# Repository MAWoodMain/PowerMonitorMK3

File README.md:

# Power Meter MK3

## The Plan

The plan is to evaluate the ADE9153 IC using an initial PCB build with mains isolation for easy development and no real planned form factor.

Then assuming the IC checks out the schematic and PCB will be reissued without isolation and with a much tigher form factor to fit in a DIN rail enclosure so it can be wired into my home.

An extra prototype run may be required inbetween to evaluate isolation removal or to fix mistakes that render ISS1 unusable.

The ISS1 PCB is powered from the safe side using a micro USB cable and this power is isolated and used on the hot side, this circuit is based on the ADE9153's evaluation board schematic. 

**It is noteworthy that the hot side's GND is mains live and does present a serious safety risk.**

I accept no liability for anyone else's use of this design.

## PCB Builds

### ISS1 Build:
- PCB ordered from JLC PCB
  - ENIG finish
  - 1.6mm FR4
  - Top side stencil order with the PCB
    - Ordered default size, this was a mistake next time order a custom side much smaller
- Parts ordered from LCSC and DigiKey kitting for 2 PCBs
  - DHL on behalf of Digikey charged excessive customs charges inflating the build cost greatly I recommend Mouser as an alternative (for the UK) and have upissued the BOM accordingly
- Assembled at home
  - Boards were cleaned with IPA
  - Scrap PCBs were used to position the new PCB in place for stenciling
  - Paste was squeegeed onto the boards using a scrap piece of ceramic with a very flat edge
  - All components were hand placed with tweezers
  - The board was placed on a temperature controlled hotplate at 150°C
  - Once the board was evenly preheated (confirmed with IR thermometer) 350°C hot air was used to reflow the components
  - Some joints were not fully reflowed so touchups were performed with a fine soldering tip and extra liquid flux
  - The ADE9153 IC is in a QFN package which is difficult to manage as a hobbiest so reflow did yield some shorts on the edges, the shorts were manually reworked with extra flux and a fine tip.
  - Fortunatly the guard trace around the VAMS did not short to GND or VAMS, the layout recommendations from AD were to expose copper under the QFN which posed a high risk of soldering shorts.
  - The board was then cleaned with flux clean and IPA
  - All hand soldered components were soldered normally
  - A final clean was performed with flux clean

#### Issues associated with this build:
[#1](/../../issues/1) [#2](/../../issues/2) [#3](/../../issues/3)
#### Board mods:
- **MOD A** 
  - Pin 5 of U2 (Isolated DC-DC) has to be isolated, the PCB connects it to GND which prevents the IC from working
     - I cut the leg off the IC to isolate it

- **MOD B** 
  - ESP32-Wrover pins 17-22 cannot be used as they are used internally
     - I cut NC jumpers JP5, JP6 & JP7, the both sides of all three jumpers is reserved for internal use so manual wire mods will be needed lated to connect these to appropriate pins

## Firmware development

Currently in hardware testing phase, temporary non VCS projects are being used to evaluate the PCB, once this process is complete a formal firmware project will be added to VCS and developed

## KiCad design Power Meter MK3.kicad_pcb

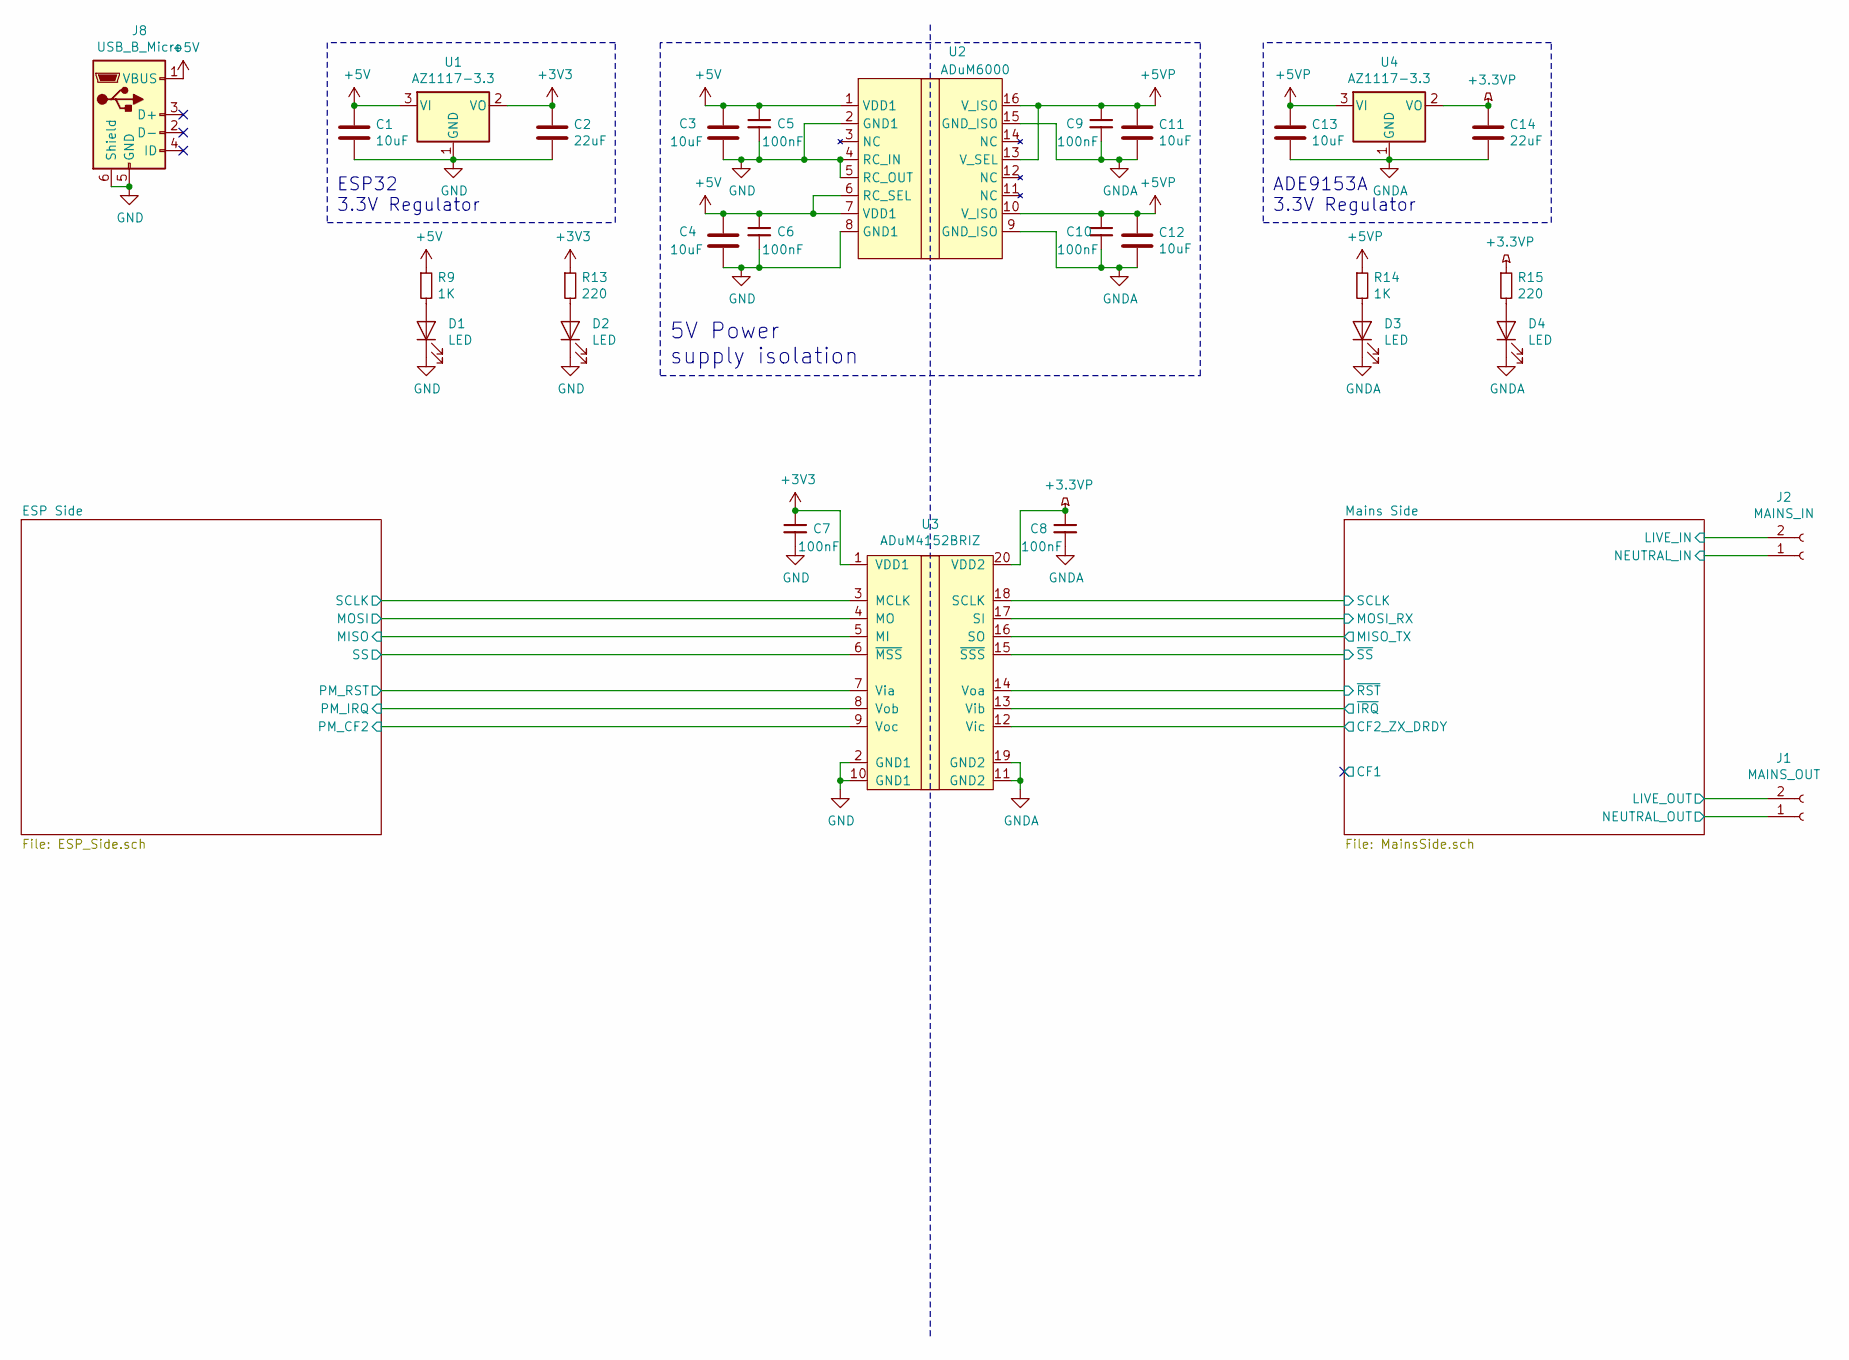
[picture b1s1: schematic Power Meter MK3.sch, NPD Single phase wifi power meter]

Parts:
C1, C3, C4, C11, C12, C13: 10uF; C_0603_1608Metric
C2, C14: 22uF; C_0603_1608Metric
C5, C6, C7, C8, C9, C10: 100nF; C_0603_1608Metric
D1, D2, D3, D4: LED; LED_0603_1608Metric
J1: MAINS_OUT; PHOENIX_1792229
J2: MAINS_IN; PHOENIX_1792229
J8: USB_B_Micro; USB_Micro-B_Molex_47346-0001
R9, R14: 1K; R_0603_1608Metric
R13, R15: 220; R_0603_1608Metric
U1, U4: AZ1117-3.3; SOT-223-3_TabPin2
U2: ADuM6000; SOIC-16W_7.5x10.3mm_P1.27mm
U3: ADuM4152BRIZ; SOIC-20W_7.5x12.8mm_P1.27mm

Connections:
+3.3VP: C8.1, C14.1, R15.1, U3.20 (VDD2), U4.2 (VO); also elsewhere on the board
+3V3: C2.1, C7.1, R13.1, U1.2 (VO), U3.1 (VDD1); also elsewhere on the board
+5V: C1.1, C3.1, C4.1, C5.1, C6.1, J8.1 (VBUS), R9.1, U1.3 (VI), U2.1 (VDD1), U2.6 (RC_SEL), U2.7 (VDD1)
+5VP: C9.1, C10.1, C11.1, C12.1, C13.1, R14.1, U2.10 (V_ISO), U2.13 (V_SEL), U2.16 (V_ISO), U4.3 (VI)
/ESP Side/MISO: U3.5 (MI); also elsewhere on the board
/ESP Side/MOSI: U3.4 (MO); also elsewhere on the board
/ESP Side/PM_CF2: U3.9 (Voc); also elsewhere on the board
/ESP Side/PM_IRQ: U3.8 (Vob); also elsewhere on the board
/ESP Side/PM_RST: U3.7 (Via); also elsewhere on the board
/ESP Side/SCLK: U3.3 (MCLK); also elsewhere on the board
/ESP Side/SS: U3.6 (~MSS); also elsewhere on the board
/Mains Side/CF2_ZX_DRDY: U3.12 (Vic); also elsewhere on the board
/Mains Side/LIVE_OUT: J1.2; also elsewhere on the board
/Mains Side/MISO_TX: U3.16 (SO); also elsewhere on the board
/Mains Side/MOSI_RX: U3.17 (SI); also elsewhere on the board
/Mains Side/NEUTRAL_IN: J1.1, J2.1; also elsewhere on the board
/Mains Side/SCLK: U3.18 (SCLK); also elsewhere on the board
/Mains Side/~IRQ: U3.13 (Vib); also elsewhere on the board
/Mains Side/~RST: U3.14 (Voa); also elsewhere on the board
/Mains Side/~SS: U3.15 (~SSS); also elsewhere on the board
GND: C1.2, C2.2, C3.2, C4.2, C5.2, C6.2, C7.2, D1.1 (K), D2.1 (K), J8.5 (GND), J8.6 (Shield), U1.1 (GND), U2.2 (GND1), U2.4 (RC_IN), U2.5 (RC_OUT), U2.8 (GND1), U3.2 (GND1), U3.10 (GND1); also elsewhere on the board
GNDA: C8.2, C9.2, C10.2, C11.2, C12.2, C13.2, C14.2, D3.1 (K), D4.1 (K), J2.2, U2.9 (GND_ISO), U2.15 (GND_ISO), U3.11 (GND2), U3.19 (GND2), U4.1 (GND); also elsewhere on the board
unnamed: D1.2 (A), R9.2
unnamed: D2.2 (A), R13.2
unnamed: D3.2 (A), R14.2
unnamed: D4.2 (A), R15.2

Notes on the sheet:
ESP32 3.3V Regulator
5V Power supply isolation
ADE9153A 3.3V Regulator

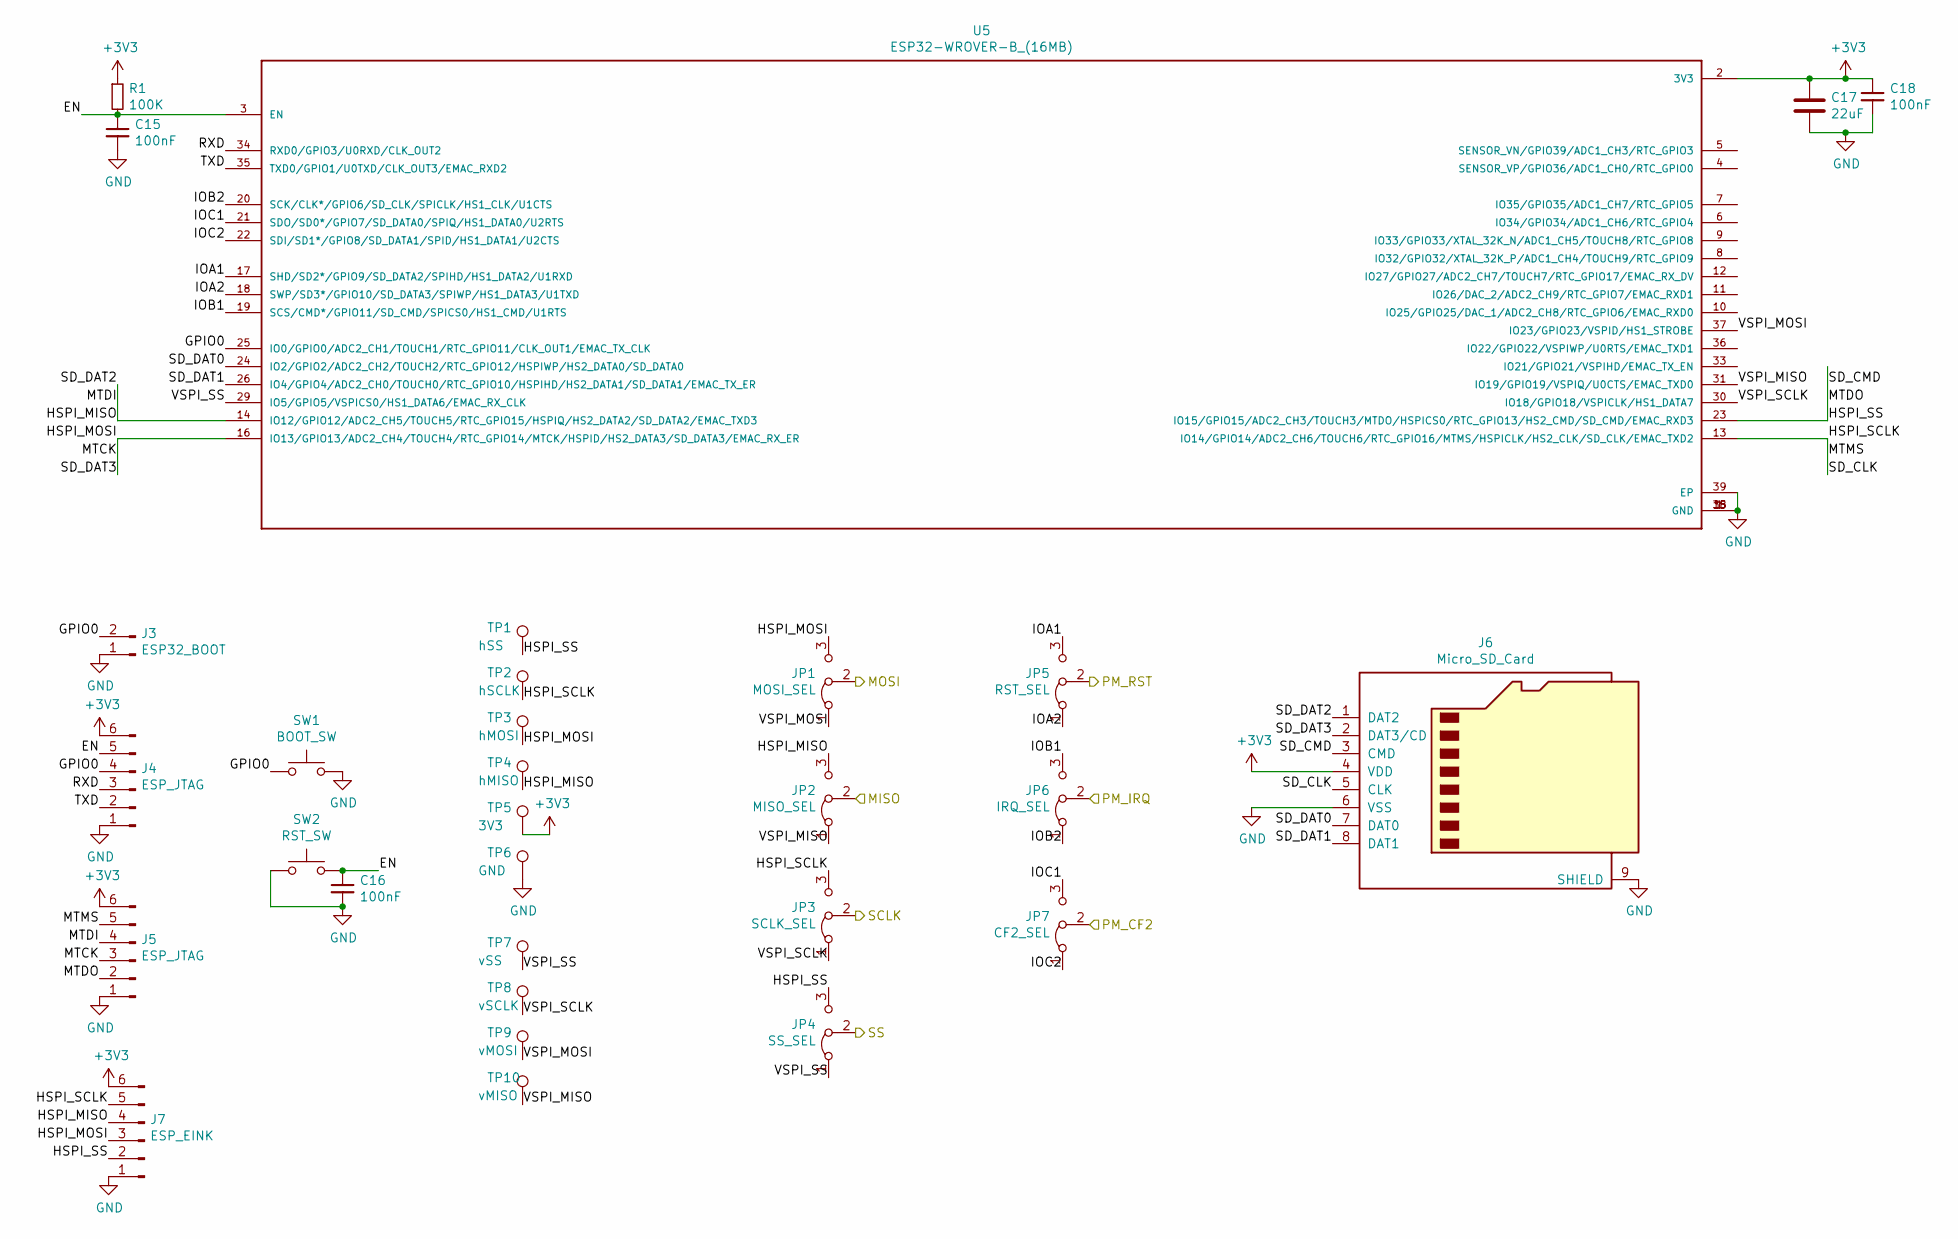
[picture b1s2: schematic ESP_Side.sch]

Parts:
C15, C16, C18: 100nF; C_0603_1608Metric
C17: 22uF; C_0603_1608Metric
J3: ESP32_BOOT; PinHeader_1x02_P2.54mm_Vertical
J4, J5: ESP_JTAG; JST_PH_B6B-PH-K_1x06_P2.00mm_Vertical
J6: Micro_SD_Card; microSD_HC_Hirose_DM3D-SF
J7: ESP_EINK; JST_PH_B6B-PH-K_1x06_P2.00mm_Vertical
JP1: MOSI_SEL; SolderJumper-3_P1.3mm_Bridged12_RoundedPad1.0x1.5mm_NumberL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
JP2: MISO_SEL; SolderJumper-3_P1.3mm_Bridged12_RoundedPad1.0x1.5mm_NumberL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
JP3: SCLK_SEL; SolderJumper-3_P1.3mm_Bridged12_RoundedPad1.0x1.5mm_NumberL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
JP4: SS_SEL; SolderJumper-3_P1.3mm_Bridged12_RoundedPad1.0x1.5mm_NumberL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
JP5: RST_SEL; SolderJumper-3_P1.3mm_Bridged12_RoundedPad1.0x1.5mm_NumberL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
JP6: IRQ_SEL; SolderJumper-3_P1.3mm_Bridged12_RoundedPad1.0x1.5mm_NumberL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
JP7: CF2_SEL; SolderJumper-3_P1.3mm_Bridged12_RoundedPad1.0x1.5mm_NumberL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
R1: 100K; R_0603_1608Metric
SW1: BOOT_SW; SW_PUSH_6mm
SW2: RST_SW; SW_PUSH_6mm
TP1: hSS; Pin_D1.0mm_L10.0mm
TP2: hSCLK; Pin_D1.0mm_L10.0mm
TP3: hMOSI; Pin_D1.0mm_L10.0mm
TP4: hMISO; Pin_D1.0mm_L10.0mm
TP5: 3V3; Pin_D1.0mm_L10.0mm
TP6: GND; Pin_D1.0mm_L10.0mm
TP7: vSS; Pin_D1.0mm_L10.0mm
TP8: vSCLK; Pin_D1.0mm_L10.0mm
TP9: vMOSI; Pin_D1.0mm_L10.0mm
TP10: vMISO; Pin_D1.0mm_L10.0mm
U5: ESP32-WROVER-B_(16MB); XCVR_ESP32-WROVER-B_(16MB)

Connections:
+3V3: C17.1, C18.1, J4.6, J5.6, J6.4 (VDD), J7.6, R1.1, TP5.1, U5.2 (3V3); also elsewhere on the board
/ESP Side/EN: C15.1, C16.1, J4.5, R1.2, SW2.2, U5.3 (EN)
/ESP Side/GPIO0: J3.2, J4.4, SW1.1, U5.25 (IO0/GPIO0/ADC2_CH1/TOUCH1/RTC_GPIO11/CL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)
/ESP Side/HSPI_MISO: J5.4, J6.1 (DAT2), J7.4, JP2.3 (B), TP4.1, U5.14 (IO12/GPIO12/ADC2_CH5/TOUCH5/RTC_GPIO15/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)
/ESP Side/HSPI_MOSI: J5.3, J6.2 (DAT3/CD), J7.3, JP1.3 (B), TP3.1, U5.16 (IO13/GPIO13/ADC2_CH4/TOUCH4/RTC_GPIO14/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)
/ESP Side/HSPI_SCLK: J5.5, J6.5 (CLK), J7.5, JP3.3 (B), TP2.1, U5.13 (IO14/GPIO14/ADC2_CH6/TOUCH6/RTC_GPIO16/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)
/ESP Side/HSPI_SS: J5.2, J6.3 (CMD), J7.2, JP4.3 (B), TP1.1, U5.23 (IO15/GPIO15/ADC2_CH3/TOUCH3/MTDO/HSPICS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)
/ESP Side/IOA1: JP5.3 (B), U5.17 (SHD/SD2*/GPIO9/SD_DATA2/SPIHD/HS1_DATA2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)
/ESP Side/IOA2: JP5.1 (A), U5.18 (SWP/SD3*/GPIO10/SD_DATA3/SPIWP/HS1_DATA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)
/ESP Side/IOB1: JP6.3 (B), U5.19 (SCS/CMD*/GPIO11/SD_CMD/SPICS0/HS1_CMD/U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)
/ESP Side/IOB2: JP6.1 (A), U5.20 (SCK/CLK*/GPIO6/SD_CLK/SPICLK/HS1_CLK/U1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)
/ESP Side/IOC1: JP7.3 (B), U5.21 (SDO/SD0*/GPIO7/SD_DATA0/SPIQ/HS1_DATA0/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)
/ESP Side/IOC2: JP7.1 (A), U5.22 (SDI/SD1*/GPIO8/SD_DATA1/SPID/HS1_DATA1/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)
/ESP Side/MISO: JP2.2 (C); also elsewhere on the board
/ESP Side/MOSI: JP1.2 (C); also elsewhere on the board
/ESP Side/PM_CF2: JP7.2 (C); also elsewhere on the board
/ESP Side/PM_IRQ: JP6.2 (C); also elsewhere on the board
/ESP Side/PM_RST: JP5.2 (C); also elsewhere on the board
/ESP Side/RXD: J4.3, U5.34 (RXD0/GPIO3/U0RXD/CLK_OUT2)
/ESP Side/SCLK: JP3.2 (C); also elsewhere on the board
/ESP Side/SD_DAT0: J6.7 (DAT0), U5.24 (IO2/GPIO2/ADC2_CH2/TOUCH2/RTC_GPIO12/HS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)
/ESP Side/SD_DAT1: J6.8 (DAT1), U5.26 (IO4/GPIO4/ADC2_CH0/TOUCH0/RTC_GPIO10/HS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)
/ESP Side/SS: JP4.2 (C); also elsewhere on the board
/ESP Side/TXD: J4.2, U5.35 (TXD0/GPIO1/U0TXD/CLK_OUT3/EMAC_RXD2)
/ESP Side/VSPI_MISO: JP2.1 (A), TP10.1, U5.31 (IO19/GPIO19/VSPIQ/U0CTS/EMAC_TXD0)
/ESP Side/VSPI_MOSI: JP1.1 (A), TP9.1, U5.37 (IO23/GPIO23/VSPID/HS1_STROBE)
/ESP Side/VSPI_SCLK: JP3.1 (A), TP8.1, U5.30 (IO18/GPIO18/VSPICLK/HS1_DATA7)
/ESP Side/VSPI_SS: JP4.1 (A), TP7.1, U5.29 (IO5/GPIO5/VSPICS0/HS1_DATA6/EMAC_RX_CLK)
GND: C15.2, C16.2, C17.2, C18.2, J3.1, J4.1, J5.1, J6.6 (VSS), J6.9 (SHIELD), J7.1, SW1.2, SW2.1, TP6.1, U5.1 (GND), U5.15 (GND), U5.38 (GND), U5.39 (EP); also elsewhere on the board

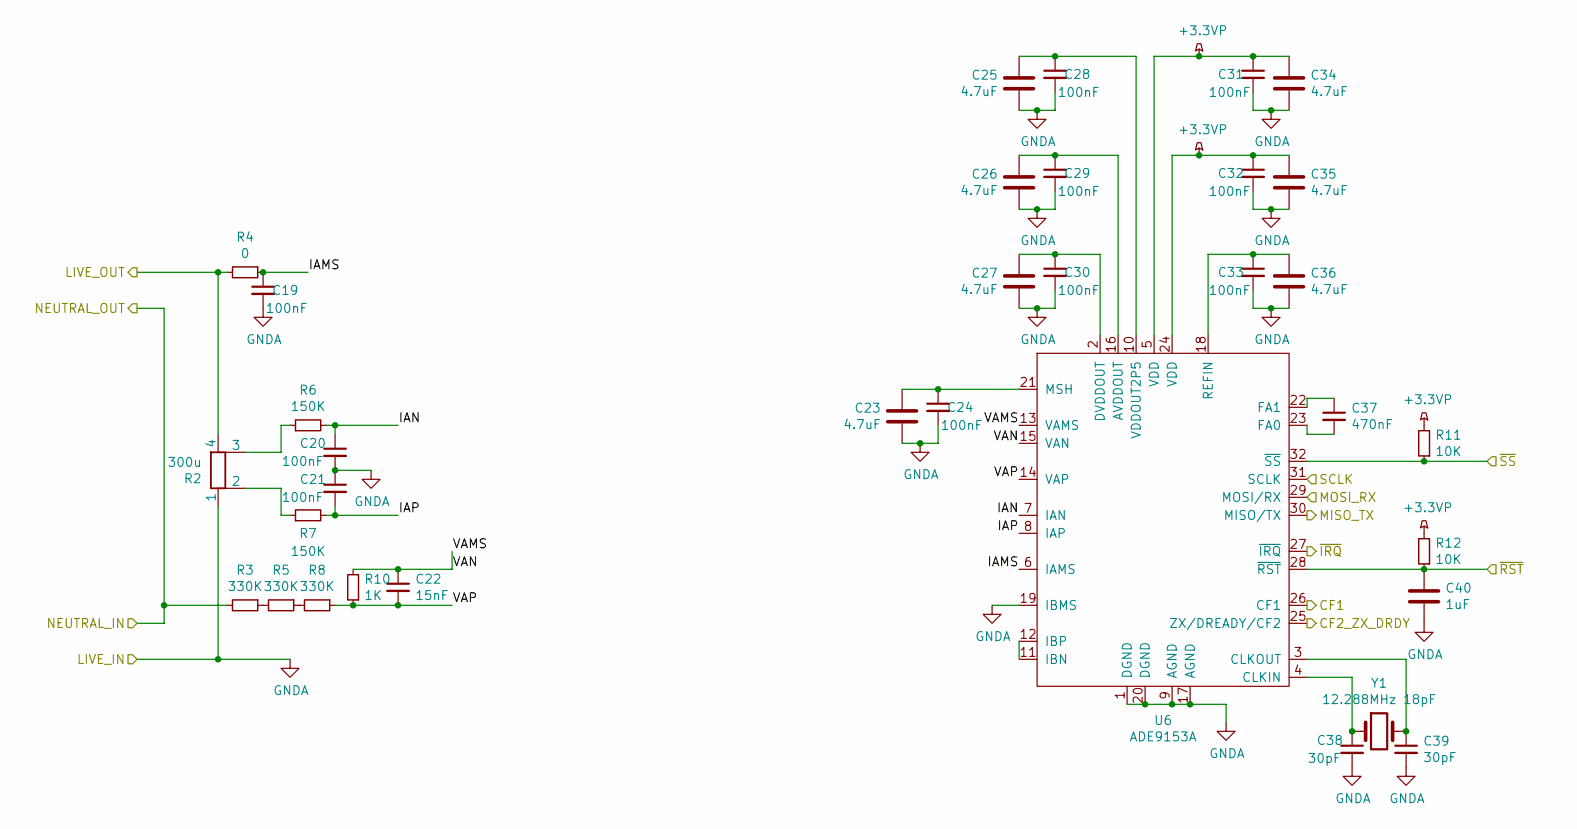
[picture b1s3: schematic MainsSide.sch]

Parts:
C19, C20, C21, C24, C28, C29, C30, C31, C32, C33: 100nF; C_0603_1608Metric
C22: 15nF; C_0603_1608Metric
C23, C25, C26, C27, C34, C35, C36: 4.7uF; C_0603_1608Metric
C37: 470nF; C_0603_1608Metric
C38, C39: 30pF; C_0603_1608Metric
C40: 1uF; C_0603_1608Metric
R2: 300u; WSL4026
R3, R5, R8: 330K; R_1206_3216Metric
R4: 0; R_0603_1608Metric
R6, R7: 150K; R_0603_1608Metric
R10: 1K; R_0603_1608Metric
R11, R12: 10K; R_0603_1608Metric
U6: ADE9153A; QFN-32-1EP_5x5mm_P0.5mm_EP3.1x3.1mm
Y1: 12.288MHz 18pF; Crystal_SMD_3225-4Pin_3.2x2.5mm

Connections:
+3.3VP: C31.1, C32.1, C34.1, C35.1, R11.2, R12.2, U6.5 (VDD), U6.24 (VDD); also elsewhere on the board
/Mains Side/CF1: U6.26 (CF1)
/Mains Side/CF2_ZX_DRDY: U6.25 (ZX/DREADY/CF2); also elsewhere on the board
/Mains Side/IAMS: C19.1, R4.1, U6.6 (IAMS)
/Mains Side/IAN: C20.1, R6.2, U6.7 (IAN)
/Mains Side/IAP: C21.2, R7.2, U6.8 (IAP)
/Mains Side/LIVE_OUT: R2.4, R4.2; also elsewhere on the board
/Mains Side/MISO_TX: U6.30 (MISO/TX); also elsewhere on the board
/Mains Side/MOSI_RX: U6.29 (MOSI/RX); also elsewhere on the board
/Mains Side/NEUTRAL_IN: R3.2; also elsewhere on the board
/Mains Side/SCLK: U6.31 (SCLK); also elsewhere on the board
/Mains Side/VAMS: C22.1, R10.2, U6.13 (VAMS), U6.15 (VAN)
/Mains Side/VAP: C22.2, R8.1, R10.1, U6.14 (VAP)
/Mains Side/~IRQ: U6.27 (~IRQ); also elsewhere on the board
/Mains Side/~RST: C40.1, R12.1, U6.28 (~RST); also elsewhere on the board
/Mains Side/~SS: R11.1, U6.32 (~SS); also elsewhere on the board
GNDA: C19.2, C20.2, C21.1, C23.2, C24.2, C25.2, C26.2, C27.2, C28.2, C29.2, C30.2, C31.2, C32.2, C33.2, C34.2, C35.2, C36.2, C38.2, C39.2, C40.2, R2.1, U6.1 (DGND), U6.9 (AGND), U6.17 (AGND), U6.19 (IBMS), U6.20 (DGND); also elsewhere on the board
unnamed: C23.1, C24.1, U6.21 (MSH)
unnamed: C25.1, C28.1, U6.10 (VDDOUT2P5)
unnamed: C26.1, C29.1, U6.16 (AVDDOUT)
unnamed: C27.1, C30.1, U6.2 (DVDDOUT)
unnamed: C33.1, C36.1, U6.18 (REFIN)
unnamed: C37.1, U6.22 (FA1)
unnamed: C37.2, U6.23 (FA0)
unnamed: C38.1, U6.4 (CLKIN), Y1.1
unnamed: C39.1, U6.3 (CLKOUT), Y1.2
unnamed: R2.2, R7.1
unnamed: R2.3, R6.1
unnamed: R3.1, R5.2
unnamed: R5.1, R8.2
unnamed: U6.11 (IBN), U6.12 (IBP)

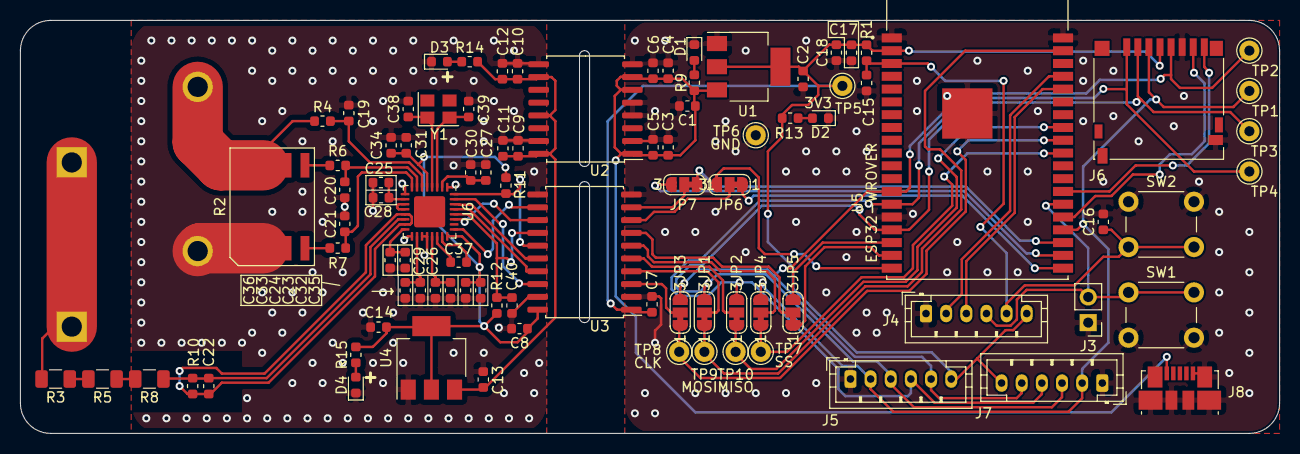
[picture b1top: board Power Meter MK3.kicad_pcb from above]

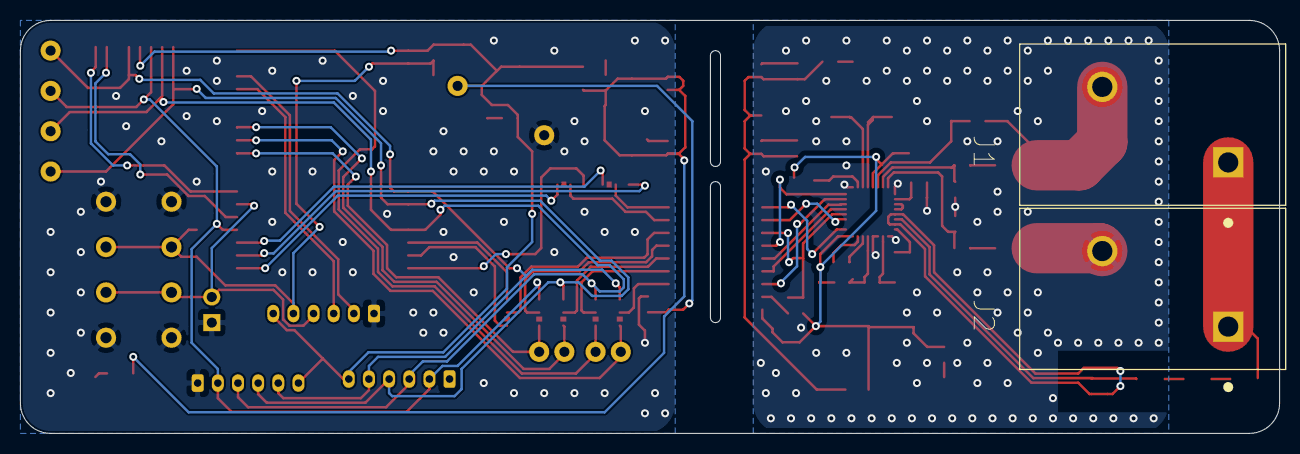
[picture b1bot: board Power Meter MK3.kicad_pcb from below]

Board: 2 copper layers, 125.0 x 41.0 mm, 93 parts (2 on the bottom side), 65 nets.

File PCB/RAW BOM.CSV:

Reference, Quantity, Value, Footprint, Datasheet, Field4, Field5, Field6, Field7, Field8
C11 C4 C3 C12 C13 C1 ,6,"10uF","Capacitor_SMD:C_0603_1608Metric","~"
C14 C2 C17 ,3,"22uF","Capacitor_SMD:C_0603_1608Metric","~"
C22 ,1,"15nF","Capacitor_SMD:C_0603_1608Metric","~"
C36 C35 C27 C34 C26 C25 C23 ,7,"4.7uF","Capacitor_SMD:C_0603_1608Metric","~"
C37 ,1,"470nF","Capacitor_SMD:C_0603_1608Metric","~"
C39 C38 ,2,"30pF","Capacitor_SMD:C_0603_1608Metric","~"
C40 ,1,"1uF","Capacitor_SMD:C_0603_1608Metric","~"
C9 C6 C5 C10 C7 C8 C18 C15 C16 C33 C32 C31 C30 C29 C28 C20 C21 C19 C24 ,19,"100nF","Capacitor_SMD:C_0603_1608Metric","~"
D4 D3 D2 D1 ,4,"LED","LED_SMD:LED_0603_1608Metric","~"
J1 ,1,"MAINS_OUT","1792229:PHOENIX_1792229","~"
J2 ,1,"MAINS_IN","1792229:PHOENIX_1792229","~"
J3 ,1,"ESP32_BOOT","Connector_PinHeader_2.54mm:PinHeader_1x02_P2.54mm_Vertical","~"
J5 J4 ,2,"ESP_JTAG","Connector_JST:JST_PH_B6B-PH-K_1x06_P2.00mm_Vertical","~"
J6 ,1,"Micro_SD_Card","Connector_Card:microSD_HC_Hirose_DM3D-SF","http://katalog.we-online.de/em/datasheet/693072010801.pdf"
J7 ,1,"ESP_EINK","Connector_JST:JST_PH_B6B-PH-K_1x06_P2.00mm_Vertical","~"
J8 ,1,"USB_B_Micro","Connector_USB:USB_Micro-B_Molex_47346-0001","~"
JP1 JP5 JP6 JP7 ,4,"MOSI_SEL","Jumper:SolderJumper-3_P1.3mm_Bridged12_RoundedPad1.0x1.5mm_NumberLabels","~"
JP2 ,1,"MISO_SEL","Jumper:SolderJumper-3_P1.3mm_Bridged12_RoundedPad1.0x1.5mm_NumberLabels","~"
JP3 ,1,"SCLK_SEL","Jumper:SolderJumper-3_P1.3mm_Bridged12_RoundedPad1.0x1.5mm_NumberLabels","~"
JP4 ,1,"SS_SEL","Jumper:SolderJumper-3_P1.3mm_Bridged12_RoundedPad1.0x1.5mm_NumberLabels","~"
R1 ,1,"100K","Resistor_SMD:R_0603_1608Metric","~"
R11 R12 ,2,"10K","Resistor_SMD:R_0603_1608Metric","~"
R14 R9 R10 ,3,"1K","Resistor_SMD:R_0603_1608Metric","~"
R15 R13 ,2,"220","Resistor_SMD:R_0603_1608Metric","~"
R2 ,1,"300u","Project:WSL4026","~"
R3 R5 R8 ,3,"330K","Resistor_SMD:R_1206_3216Metric","~"
R4 ,1,"0","Resistor_SMD:R_0603_1608Metric","~"
R6 R7 ,2,"150K","Resistor_SMD:R_0603_1608Metric","~"
SW1 ,1,"BOOT_SW","Button_Switch_THT:SW_PUSH_6mm","~"
SW2 ,1,"RST_SW","Button_Switch_THT:SW_PUSH_6mm","~"
TP1 ,1,"hSS","Connector_Pin:Pin_D1.0mm_L10.0mm","~"
TP10 ,1,"vMISO","Connector_Pin:Pin_D1.0mm_L10.0mm","~"
TP2 ,1,"hSCLK","Connector_Pin:Pin_D1.0mm_L10.0mm","~"
TP3 ,1,"hMOSI","Connector_Pin:Pin_D1.0mm_L10.0mm","~"
TP4 ,1,"hMISO","Connector_Pin:Pin_D1.0mm_L10.0mm","~"
TP5 ,1,"3V3","Connector_Pin:Pin_D1.0mm_L10.0mm","~"
TP6 ,1,"GND","Connector_Pin:Pin_D1.0mm_L10.0mm","~"
TP7 ,1,"vSS","Connector_Pin:Pin_D1.0mm_L10.0mm","~"
TP8 ,1,"vSCLK","Connector_Pin:Pin_D1.0mm_L10.0mm","~"
TP9 ,1,"vMOSI","Connector_Pin:Pin_D1.0mm_L10.0mm","~"
U2 ,1,"ADuM6000","Package_SO:SOIC-16W_7.5x10.3mm_P1.27mm","https://www.analog.com/media/en/technical-documentation/data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"
U3 ,1,"ADuM4152BRIZ","Package_SO:SOIC-20W_7.5x12.8mm_P1.27mm","https://www.analog.com/media/en/technical-documentation/data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"
U4 U1 ,2,"AZ1117-3.3","Package_TO_SOT_SMD:SOT-223-3_TabPin2","https://www.diodes.com/assets/Datasheets/AZ1117.pdf"
U5 ,1,"ESP32-WROVER-B_(16MB)","ESP32-WROVER-B__16MB_:XCVR_ESP32-WROVER-B_(16MB)","","Unavailable","Espressif Systems","None","None","ESP32-WROVER-B _16MB_"
U6 ,1,"ADE9153A","Package_DFN_QFN:QFN-32-1EP_5x5mm_P0.5mm_EP3.1x3.1mm",""
Y1 ,1,"12.288MHz 18pF","Crystal:Crystal_SMD_3225-4Pin_3.2x2.5mm","~"

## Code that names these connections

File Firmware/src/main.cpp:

#include <WiFi.h>
#include "../include/ota.h"
#include "../include/aws.h"
#include <SPI.h>
#include "../lib/ADE9153A/ADE9153A.h"
#include "../lib/ADE9153A/ADE9153AAPI.h"

#include "../include/secrets.h"

#define PM_RST 32 /* Pin 8 */
#define PM_IRQ 33 /* Pin 9 */
#define PM_CF2 27 /* Pin 12 */
#define PM_SS 5 /* Pin 29 */
#define SPI_MISO 19 /* VSPI Pin 31 */
#define SPI_MOSI 23 /* VSPI Pin 37 */
#define SPI_SCLK 18 /* VSPI Pin 30 */


#define SPI_SPEED 1000000     //SPI Speed

ADE9153AClass ade9153A;

struct EnergyRegs energyVals;
struct PowerRegs powerVals;
struct RMSRegs rmsVals;  
struct PQRegs pqVals;
struct AcalRegs acalVals;
struct Temperature tempVal;

unsigned long lastReport = 0;
const long reportInterval = 2000;

void readandwrite(void);

void setup() {
  Serial.begin(115200);
  Serial.println("Booting");
  WiFi.mode(WIFI_STA);
  WiFi.begin(WIFI_SSID, WIFI_PASS);
  while (WiFi.waitForConnectResult() != WL_CONNECTED) {
    Serial.println("Connection Failed! Rebooting...");
    delay(5000);
    ESP.restart();
  }

  Serial.println("Ready");
  Serial.print("IP address: ");
  Serial.println(WiFi.localIP());
  ota_configure();

  xTaskCreate(
    ota_task,               /* Task function. */
    "OTA_TASK",             /* String with name of task. */
    10000,                  /* Stack size in bytes. */
    NULL,                   /* Parameter passed as input of the task */
    1,                      /* Priority of the task. */
    NULL);                  /* Task handle. */

  xTaskCreatePinnedToCore(
    &aws_shadow_update_task,/* Task function. */
    "aws_iot_task",         /* String with name of task. */
    9216,                   /* Stack size in bytes. */
    NULL,                   /* Parameter passed as input of the task */
    5,                      /* Priority of the task. */
    NULL,                   /* Task handle. */
    1);                     /* The core to run the task on */


  pinMode(PM_SS, OUTPUT);
  pinMode(PM_RST, OUTPUT);
  pinMode(SPI_SCLK, OUTPUT);
  digitalWrite(PM_SS, LOW);
  digitalWrite(SPI_SCLK, HIGH);

  
  digitalWrite(PM_RST, LOW);
  delay(100);
  digitalWrite(PM_RST, HIGH);
  delay(1000);

  delay(1000);
  /*SPI initialization and test*/
  bool commscheck = ade9153A.SPI_Init(SPI_SPEED, PM_SS); //Initialize SPI
  if (!commscheck) {
    Serial.println("ADE9153A Shield not detected. Plug in Shield and reset the Arduino");
    while (!commscheck) {     //Hold until arduino is reset
      delay(1000);
    }
  }
  
  ade9153A.SetupADE9153A(); //Setup ADE9153A according to ADE9153AAPI.h
  /* Read and Print Specific Register using ADE9153A SPI Library */
  Serial.println(String(ade9153A.SPI_Read_32(REG_VERSION_PRODUCT), HEX)); // Version of IC
  ade9153A.SPI_Write_32(REG_AIGAIN, -268435456); //AIGAIN to -1 to account for IAP-IAN swap
  delay(500); 
  return;
}

void loop() 
{
  unsigned long currentReport = millis();
  
  if ((currentReport - lastReport) >= reportInterval){
    lastReport = currentReport;
    readandwrite();
  }
}

void readandwrite()
{ 
 /* Read and Print WATT Register using ADE9153A Read Library */
  ade9153A.ReadPowerRegs(&powerVals);    //Template to read Power registers from ADE9000 and store data in Arduino MCU
  ade9153A.ReadRMSRegs(&rmsVals);
  ade9153A.ReadPQRegs(&pqVals);
  ade9153A.ReadTemperature(&tempVal);
  
  Serial.printf("RMS Current:\t%.3f A\n\r", rmsVals.CurrentRMSValue/1000);
  Serial.printf("RMS Voltage:\t%.3f V\n\r", rmsVals.VoltageRMSValue/1000);
  
  Serial.print("Active Power:\t");        
  Serial.print(powerVals.ActivePowerValue/1000);
  Serial.println(" W");
  
  Serial.print("Reactive Power:\t");        
  Serial.print(powerVals.FundReactivePowerValue/1000);
  Serial.println(" VAR");
  
  Serial.print("Apparent Power:\t");        
  Serial.print(powerVals.ApparentPowerValue/1000);
  Serial.println(" VA");
  
  Serial.print("Power Factor:\t");        
  Serial.println(pqVals.PowerFactorValue);
  
  Serial.print("Frequency:\t");        
  Serial.print(pqVals.FrequencyValue);
  Serial.println(" Hz");
  
  Serial.print("Temperature:\t");        
  Serial.print(tempVal.TemperatureVal);
  Serial.println(" degC");

  Serial.println("");
  Serial.println("");
}

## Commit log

2019-06-02 Respec'd digikey parts to Mouser due to price
    Digikey lost the price war on all parts and charged a large import charge to get them in the UK, Mouser is proving a much more sensible supplier for me.
2019-06-02 Moved image to img folder
2019-06-02 Refactored project
2019-06-02 Moved PCB files into folder
2019-06-02 Added Gerbers and PDF's ISS1
2019-06-02 Moved readme back (whoops)
2019-12-02 First stage initial FW, based on analog devices ADE9153A library, rewrite pending.
    Supports Arduino OTA and AWS shadow
2019-12-02 Beginning to calculate CCs for my design
2019-12-03 Increase constants precision to 6SF throughout and found an app note fix from the forums
2019-12-03 Updated ADE CC values as per recent appnote revelations, data looking better, still not sure about the power values. Need to get auto calibration going next
